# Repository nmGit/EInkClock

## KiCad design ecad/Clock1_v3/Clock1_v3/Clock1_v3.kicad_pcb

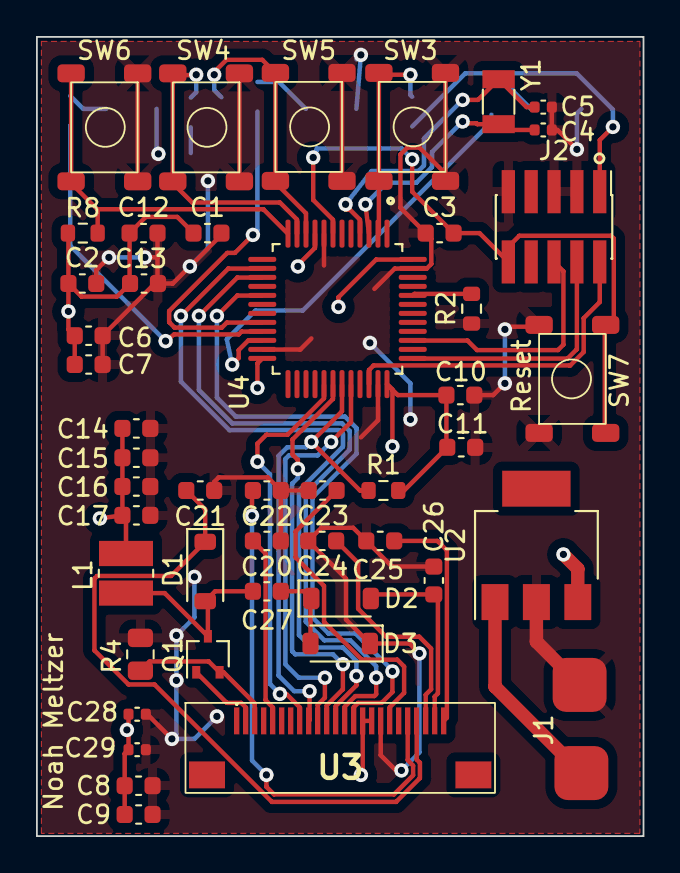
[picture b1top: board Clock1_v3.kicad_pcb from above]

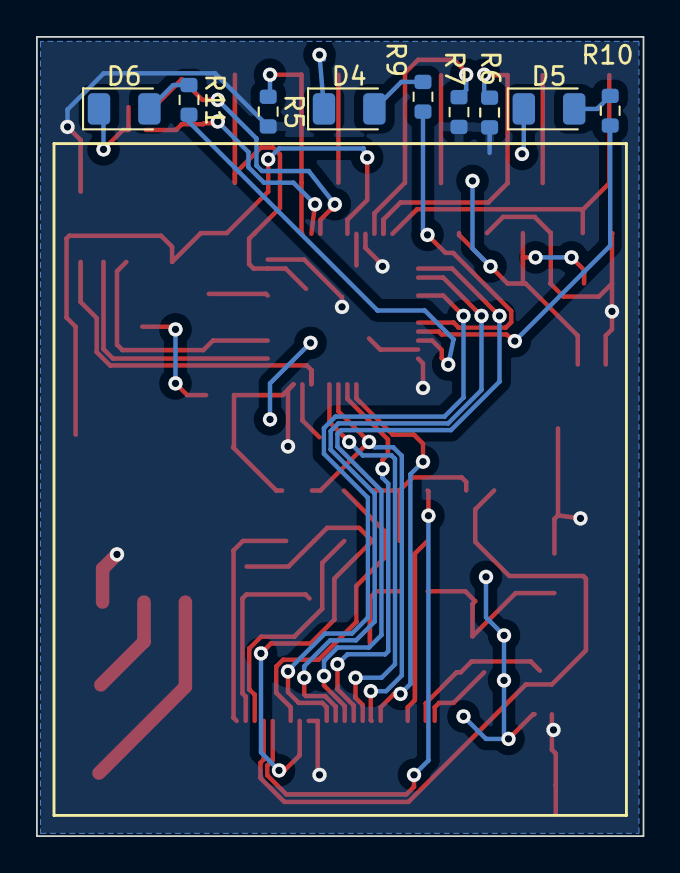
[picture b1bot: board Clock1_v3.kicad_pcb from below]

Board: 2 copper layers, 33.7 x 44.4 mm, 56 parts (9 on the bottom side), 38 nets.

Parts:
C1, C3, C6, C7, C8, C9, C10, C11, C12, C13, C14, C15, C16, C17: 100nf; C_0603_1608Metric
C2: 1uf; C_0603_1608Metric
C4, C5: 10pf; C_0402_1005Metric
C20, C21, C22, C23, C24, C25, C26: 1uF / 25V; C_0603_1608Metric
C27: 4.7uF / 25V; C_0603_1608Metric
C28: 1uF / 6.3V; C_0402_1005Metric
C29: 0.1uF / 16V; C_0402_1005Metric
D1, D2, D3: SD103AW; D_SOD-123
D4, D5, D6: LED; LED_1206_3216Metric
J1: Barrel_Jack; PowerPads
J2: Conn_ARM_JTAG_SWD_10; PinHeader_2x05_P1.27mm_Vertical_SMD
L1: 10uH; L_Ferrocore_DLG-0302
Q1: NMOS; SOT-323_SC-70
R1, R5, R6, R7, R8: 1K; R_0603_1608Metric
R2: 10K; R_0603_1608Metric
R4: 0.47R; R_0805_2012Metric
R9, R10, R11: 470; R_0603_1608Metric
SW3, SW4, SW5, SW6, SW7: SW_Push; PTS526
U2: SOT-223
U3: KH-FG0.5-H2.0-24PIN
U4: STM32F103C8T6; LQFP-48
Y1: 32k; Crystal_SMD_3215-2Pin_3.2x1.5mm

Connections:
/BOOT0: R2.2, U4.44 (BOOT0)
/LED1: R11.2, U4.22 (PB11)
/LED2: R10.2, U4.21 (PB10)
/LED3: R9.2, U4.20 (PB2)
/OSC32_IN: C4.2, U4.3 (PC14-OSC32_IN), Y1.1
/OSC32_OUT: C5.2, U4.4 (PC15-OSC32_OUT), Y1.2
/PB1: R5.1, SW3.2, U4.2 (PC13-TAMPER-RTC)
/PB2: R6.1, SW4.2, U4.11 (PA1)
/PB3: R7.1, SW5.2, U4.10 (PA0_WKUP)
/PB4: R8.1, SW6.2, U4.12 (PA2)
/SWDCLK: J2.4 (SWDCLK/TCK), U4.37 (PA14)
/SWDIO: J2.2 (SWDIO/TMS), U4.34 (PA13)
/SWO: J2.6 (SWO/TDO), U4.39 (PB3)
/epaper/epaper.gpio_bs: U3.8 (BS), U4.29 (PA8)
/epaper/epaper.gpio_busy_n: R1.1, U3.9 (BUSY), U4.31 (PA10)
/epaper/epaper.gpio_dc: U3.11 (D/C), U4.30 (PA9)
/epaper/epaper.gpio_reset_n: U3.10 (RESET), U4.32 (PA11)
/epaper/epaper.spi_cs: U3.12 (CS), U4.14 (PA4)
/epaper/epaper.spi_scl: U3.13 (SCL), U4.15 (PA5)
/epaper/epaper.spi_sda: U3.14 (SDA), U4.17 (PA7)
/nRESET: C3.2, J2.10 (~RESET), SW7.2, U4.7 (NRST)
GND: C1.2, C2.2, C3.1, C4.1, C5.1, C6.2, C7.2, C8.2, C9.2, C10.2, C11.2, C12.2, C13.2, C14.2, C15.2, C16.2, C17.2, C20.1, C21.1, C22.1, C23.1, C24.1, C25.1, C26.1, C28.2, C29.2, D3.1 (K), D4.1 (K), D5.1 (K), D6.1 (K), J1.2, J2.3 (GND), J2.5 (GND), J2.9 (GNDDetect), R2.1, R4.1, SW3.1, SW4.1, SW5.1, SW6.1, SW7.1, U2.2 (GND), U3.17 (GND), U4.8 (VSSA), U4.23 (VSS), U4.35 (VSS__1), U4.47 (VSS__2)
unnamed: C27.1, D1.2 (A), L1.2, Q1.3 (D)
unnamed: C21.2, D1.1 (K), U3.21 (VGH)
unnamed: C26.2, D2.2 (A), U3.23 (VGL)
unnamed: C27.2, D2.1 (K), D3.2 (A)
unnamed: D4.2 (A), R9.1
unnamed: D5.2 (A), R10.1
unnamed: D6.2 (A), R11.1
unnamed: Q1.1 (G), U3.2 (GDR)
unnamed: Q1.2 (S), R4.2, U3.3 (RSE)
unnamed: C25.2, U3.24 (VCOM)
unnamed: C23.2, U3.18 (VDDD)
unnamed: C22.2, U3.20 (VDH)
unnamed: C24.2, U3.22 (VDL)
unnamed: C20.2, U3.5 (VHDR)
VDD: C1.1, C2.1, C6.1, C7.1, C8.1, C9.1, C10.1, C11.1, C12.1, C13.1, C14.1, C15.1, C16.1, C17.1, C28.1, C29.1, J2.1 (VTref), L1.1, R1.2, R5.2, R6.2, R7.2, R8.2, U2.3 (Vout), U3.15 (VDDIO), U3.16 (VDDA), U4.9 (VDDA), U4.24 (VDD), U4.36 (VDD__1), U4.48 (VDD__2)
Vin: J1.1, U2.1 (Vin)

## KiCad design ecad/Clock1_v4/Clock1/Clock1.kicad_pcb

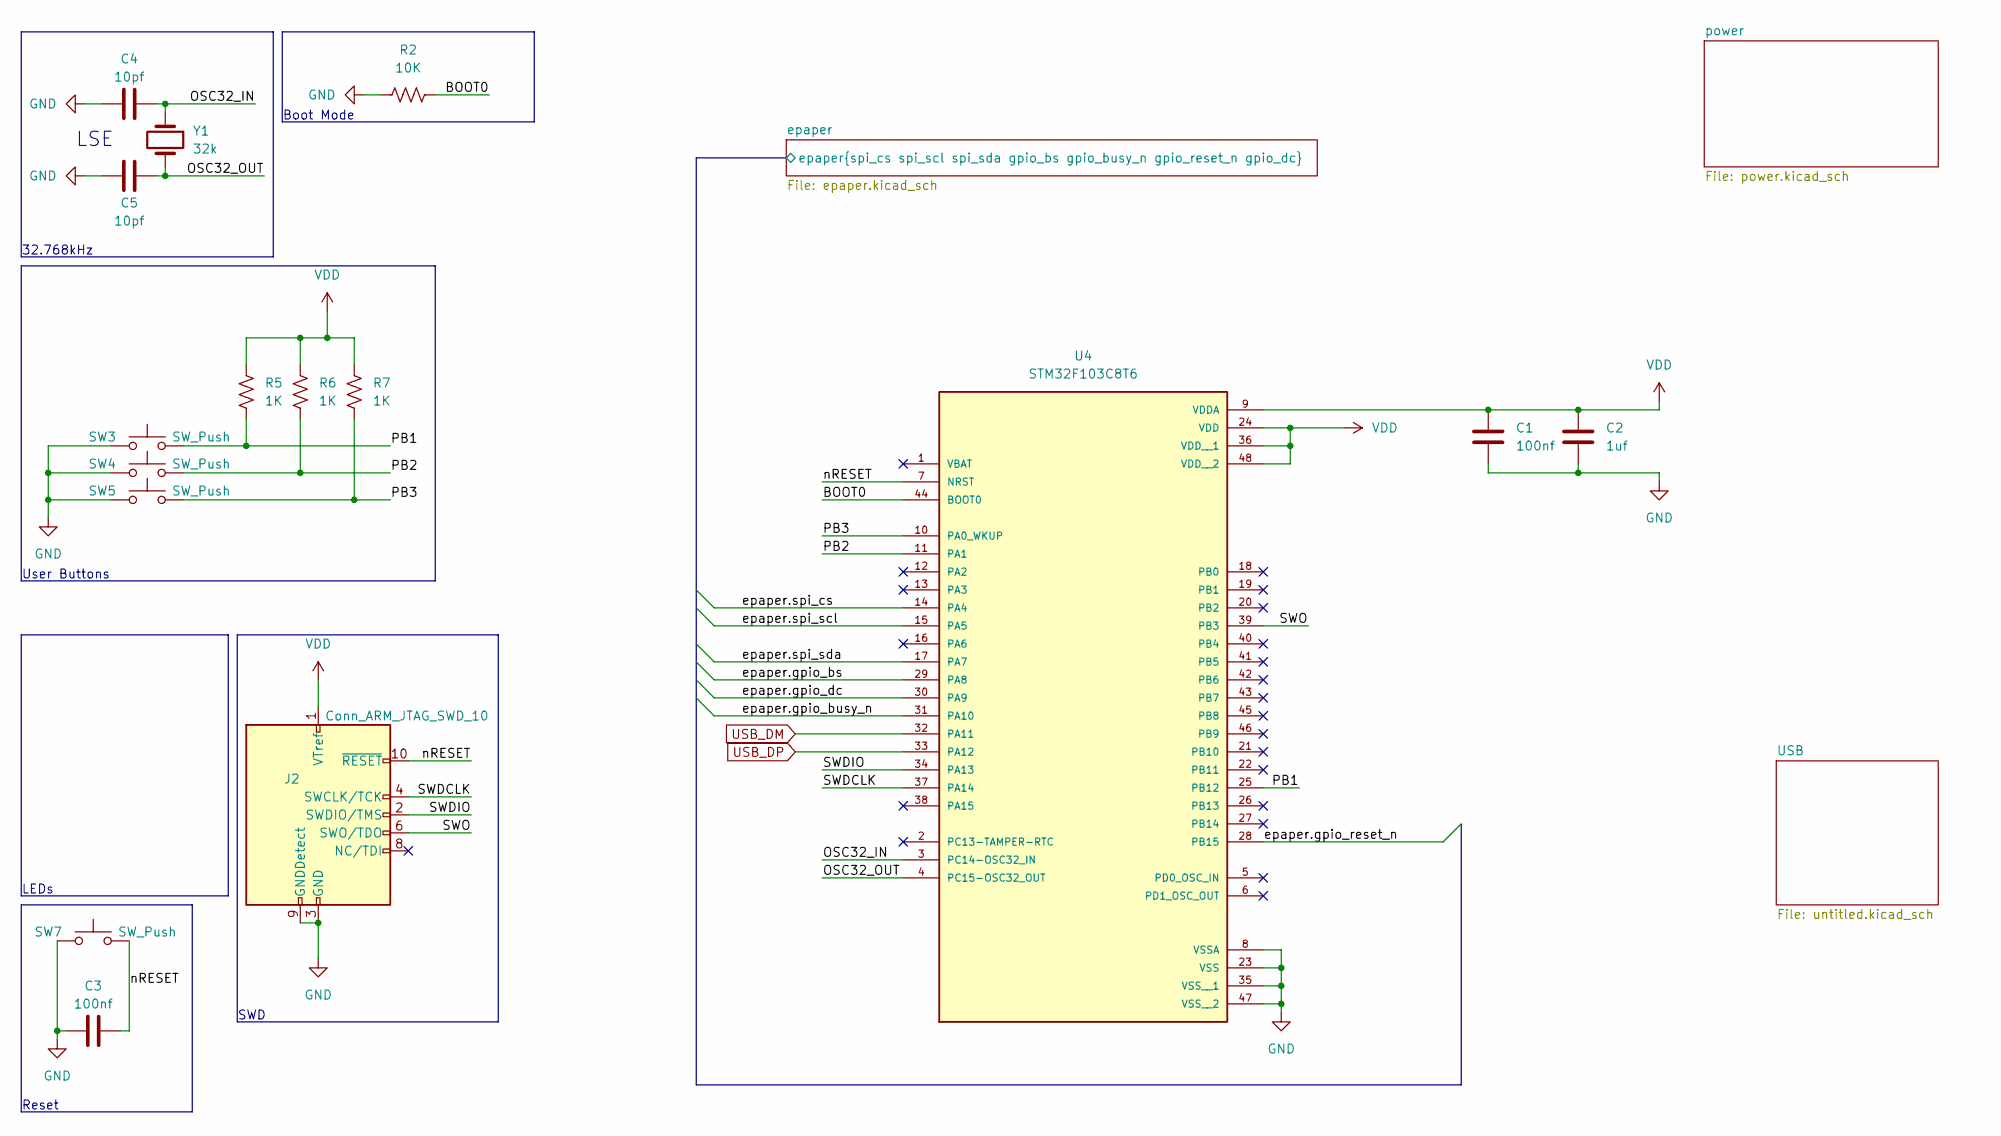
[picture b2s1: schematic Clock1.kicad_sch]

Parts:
C1, C3: 100nf; C_0603_1608Metric; Part Number KAM15AR71H104KT; JLCPCB Part # C14663
C2: 1uf; C_0603_1608Metric; Part Number MSASU168AB7105KTNA01; JLCPCB Part # C90540
C4, C5: 10pf; C_0402_1005Metric; Part Number C0402C0G100J500NTB; JLCPCB Part # C115606
J2: Conn_ARM_JTAG_SWD_10; PinHeader_2x05_P1.27mm_Vertical_SMD; Part Number 20021121-00010T4LF; JLCPCB Part # C598540
R2: 10K; R_0603_1608Metric; Part Number CRCW060310K0DHEAP; JLCPCB Part # C25804
R5, R6, R7: 1K; R_0603_1608Metric; Part Number AC0603JR-071KL; JLCPCB Part # C144622
SW3, SW4, SW5, SW7: SW_Push; PTS526; Part Number PTS526SM15SMTR2LFS; JLCPCB Part # C2689538
U4: STM32F103C8T6; LQFP-48; PARTREV 10; JLCPCB Part # C8734
Y1: 32k; Crystal_SMD_3215-2Pin_3.2x1.5mm; Part Number SF32K32768D91T-B; JLCPCB Part # C907542

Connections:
/BOOT0: R2.2, U4.44 (BOOT0)
/OSC32_IN: C4.2, U4.3 (PC14-OSC32_IN), Y1.1
/OSC32_OUT: C5.2, U4.4 (PC15-OSC32_OUT), Y1.2
/PB1: R5.1, SW3.2, U4.25 (PB12)
/PB2: R6.1, SW4.2, U4.11 (PA1)
/PB3: R7.1, SW5.2, U4.10 (PA0_WKUP)
/SWDCLK: J2.4 (SWCLK/TCK), U4.37 (PA14)
/SWDIO: J2.2 (SWDIO/TMS), U4.34 (PA13)
/SWO: J2.6 (SWO/TDO), U4.39 (PB3)
/epaper/epaper.gpio_bs: U4.29 (PA8); also elsewhere on the board
/epaper/epaper.gpio_busy_n: U4.31 (PA10); also elsewhere on the board
/epaper/epaper.gpio_dc: U4.30 (PA9); also elsewhere on the board
/epaper/epaper.gpio_reset_n: U4.28 (PB15); also elsewhere on the board
/epaper/epaper.spi_cs: U4.14 (PA4); also elsewhere on the board
/epaper/epaper.spi_scl: U4.15 (PA5); also elsewhere on the board
/epaper/epaper.spi_sda: U4.17 (PA7); also elsewhere on the board
/nRESET: C3.2, J2.10 (~RESET), SW7.2, U4.7 (NRST)
GND: C1.2, C2.2, C3.1, C4.1, C5.1, J2.3 (GND), J2.5 (GND), J2.9 (GNDDetect), R2.1, SW3.1, SW4.1, SW5.1, SW7.1, U4.8 (VSSA), U4.23 (VSS), U4.35 (VSS__1), U4.47 (VSS__2); also elsewhere on the board
USB_DM: U4.32 (PA11); also elsewhere on the board
USB_DP: U4.33 (PA12); also elsewhere on the board
VDD: C1.1, C2.1, J2.1 (VTref), R5.2, R6.2, R7.2, U4.9 (VDDA), U4.24 (VDD), U4.36 (VDD__1), U4.48 (VDD__2); also elsewhere on the board

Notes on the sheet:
Boot Mode
User Buttons
LSE
32.768kHz
SWD
LEDs
Reset

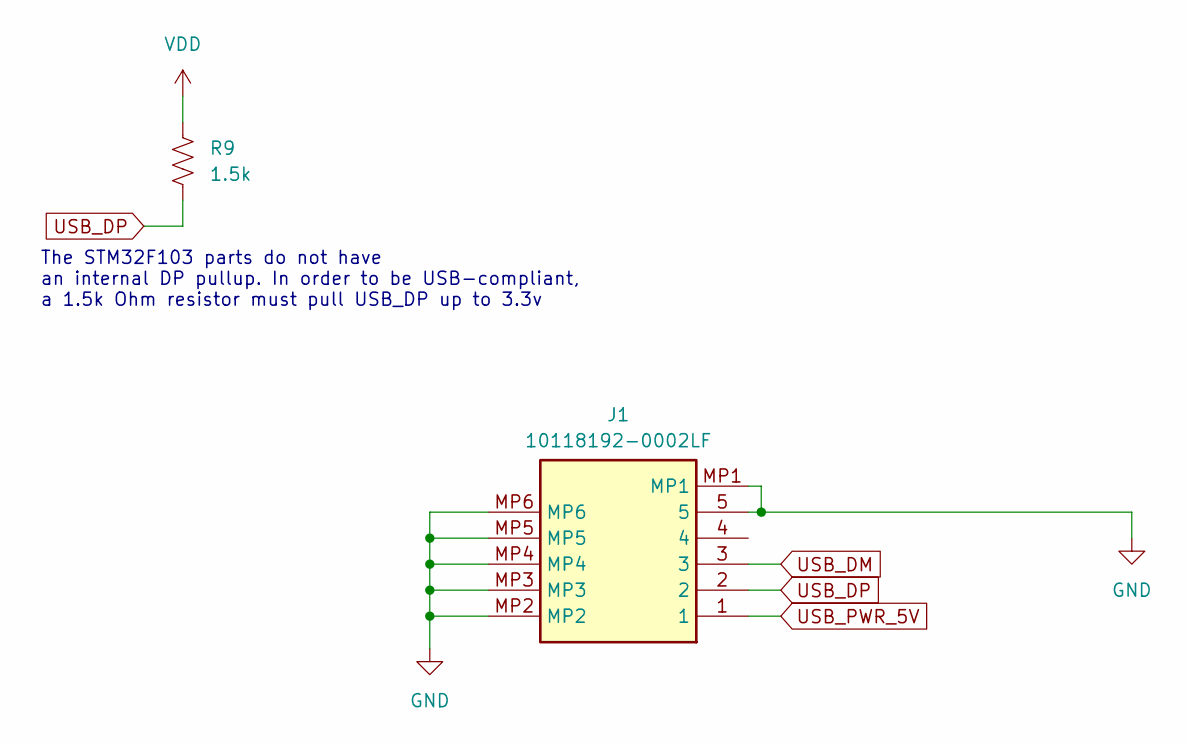
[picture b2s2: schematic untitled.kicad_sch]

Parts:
J1: 10118192-0002LF; 101181920002LF; Manufacturer_Part_Number 10118192-0002LF; JLCPCB Part # C2972784
R9: 1.5k; R_0402_1005Metric; Part Number RTT021501FTH; JLCPCB Part # C102811

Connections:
GND: J1.5, J1.MP1, J1.MP2, J1.MP3, J1.MP4, J1.MP5, J1.MP6; also elsewhere on the board
USB_DM: J1.3; also elsewhere on the board
USB_DP: J1.2, R9.2; also elsewhere on the board
USB_PWR_5V: J1.1; also elsewhere on the board
VDD: R9.1; also elsewhere on the board

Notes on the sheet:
The STM32F103 parts do not have an internal DP pullup. In order to be USB-compliant, a 1.5k Ohm resistor must pull USB_DP up to 3.3v

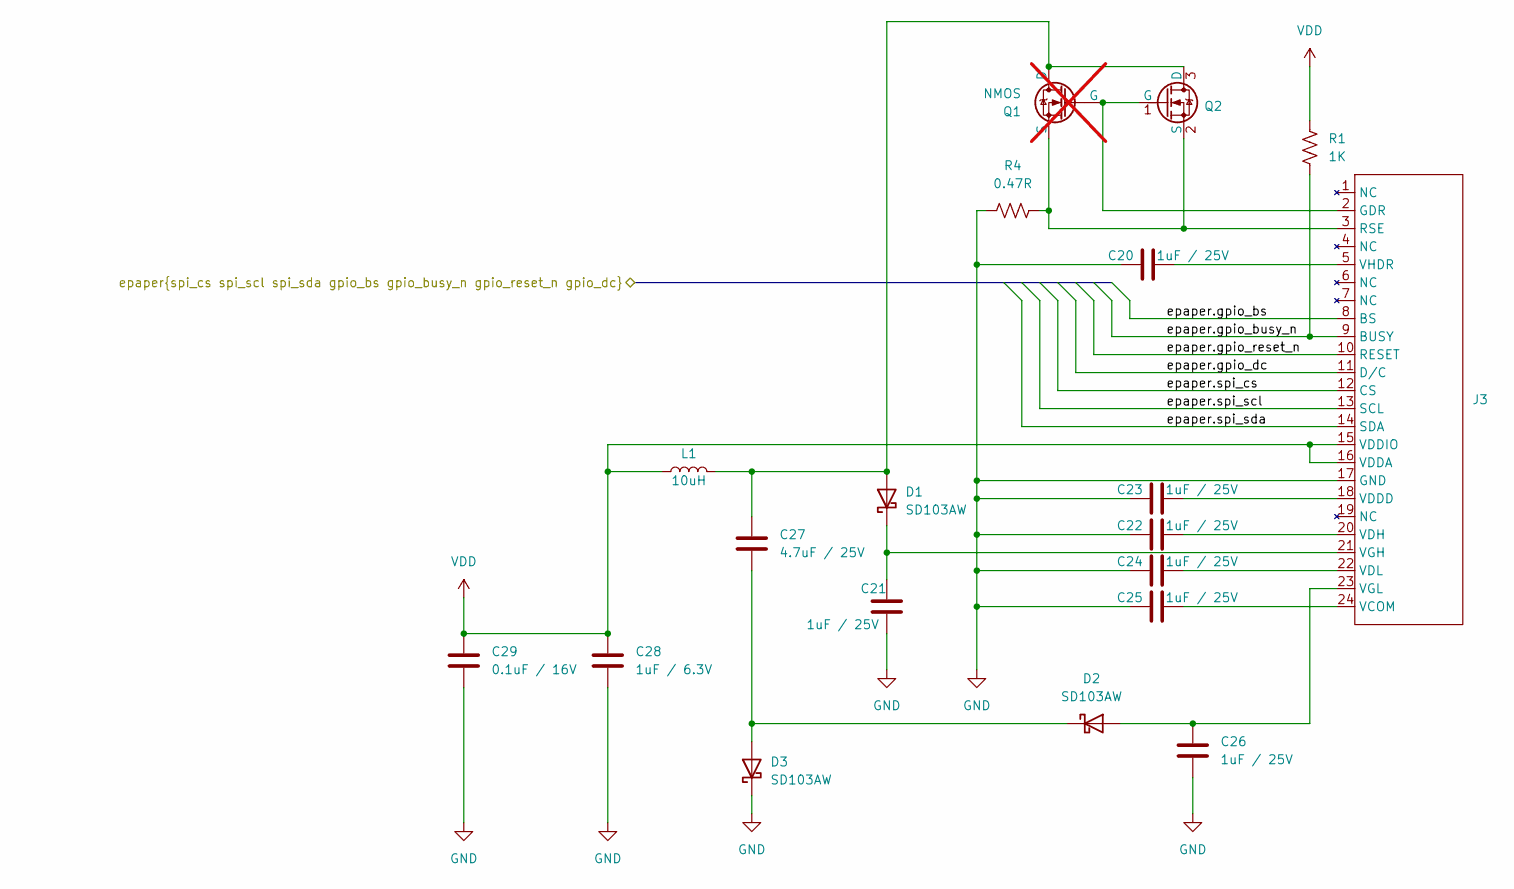
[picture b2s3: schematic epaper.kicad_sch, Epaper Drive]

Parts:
C20, C21, C22, C23, C24, C25, C26: 1uF / 25V; C_0603_1608Metric; Part Number CC0603KRX7R8BB105; JLCPCB Part # C106858
C27: 4.7uF / 25V; C_0603_1608Metric; Part Number C1608X5R1E475KT000E; JLCPCB Part # C76615
C28: 1uF / 6.3V; C_0402_1005Metric; Part Number C1005X5R105KCT; JLCPCB Part # C258509
C29: 0.1uF / 16V; C_0402_1005Metric; Part Number V105K0402X5R160NBT; JLCPCB Part # C3009903
D1, D2, D3: SD103AW; D_SOD-123; Part Number SD103AW; JLCPCB Part # C181204
J3: KH-FG0.5-H2.0-24PIN; Part Number KH-FG0.5-H2.0-24PIN; JLCPCB Part # C2797213
L1: 10uH; L_Ferrocore_DLG-0302; Part Number CD32YP0302-100M; JLCPCB Part # C492261
Q1: NMOS; SOT-323_SC-70; Part Number RTF016N05TL; JLCPCB Part # C3282000; not fitted
Q2: SOT-23; Part Number PJM02N60SA; JLCPCB Part # C2856840
R1: 1K; R_0603_1608Metric; Part Number AC0603JR-071KL; JLCPCB Part # C144622
R4: 0.47R; R_0805_2012Metric; Part Number ERJ-U6QJR47V; JLCPCB Part # C491238

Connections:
/epaper/epaper.gpio_bs: J3.8 (BS); also elsewhere on the board
/epaper/epaper.gpio_busy_n: J3.9 (BUSY), R1.1; also elsewhere on the board
/epaper/epaper.gpio_dc: J3.11 (D/C); also elsewhere on the board
/epaper/epaper.gpio_reset_n: J3.10 (RESET); also elsewhere on the board
/epaper/epaper.spi_cs: J3.12 (CS); also elsewhere on the board
/epaper/epaper.spi_scl: J3.13 (SCL); also elsewhere on the board
/epaper/epaper.spi_sda: J3.14 (SDA); also elsewhere on the board
GND: C20.1, C21.1, C22.1, C23.1, C24.1, C25.1, C26.1, C28.2, C29.2, D3.1 (K), J3.17 (GND), R4.1; also elsewhere on the board
unnamed: C27.1, D1.2 (A), L1.2, Q1.1 (D), Q2.3 (D)
unnamed: C21.2, D1.1 (K), J3.21 (VGH)
unnamed: C26.2, D2.2 (A), J3.23 (VGL)
unnamed: C27.2, D2.1 (K), D3.2 (A)
unnamed: J3.2 (GDR), Q1.2 (G), Q2.1 (G)
unnamed: J3.3 (RSE), Q1.3 (S), Q2.2 (S), R4.2
unnamed: C25.2, J3.24 (VCOM)
unnamed: C23.2, J3.18 (VDDD)
unnamed: C22.2, J3.20 (VDH)
unnamed: C24.2, J3.22 (VDL)
unnamed: C20.2, J3.5 (VHDR)
VDD: C28.1, C29.1, J3.15 (VDDIO), J3.16 (VDDA), L1.1, R1.2; also elsewhere on the board

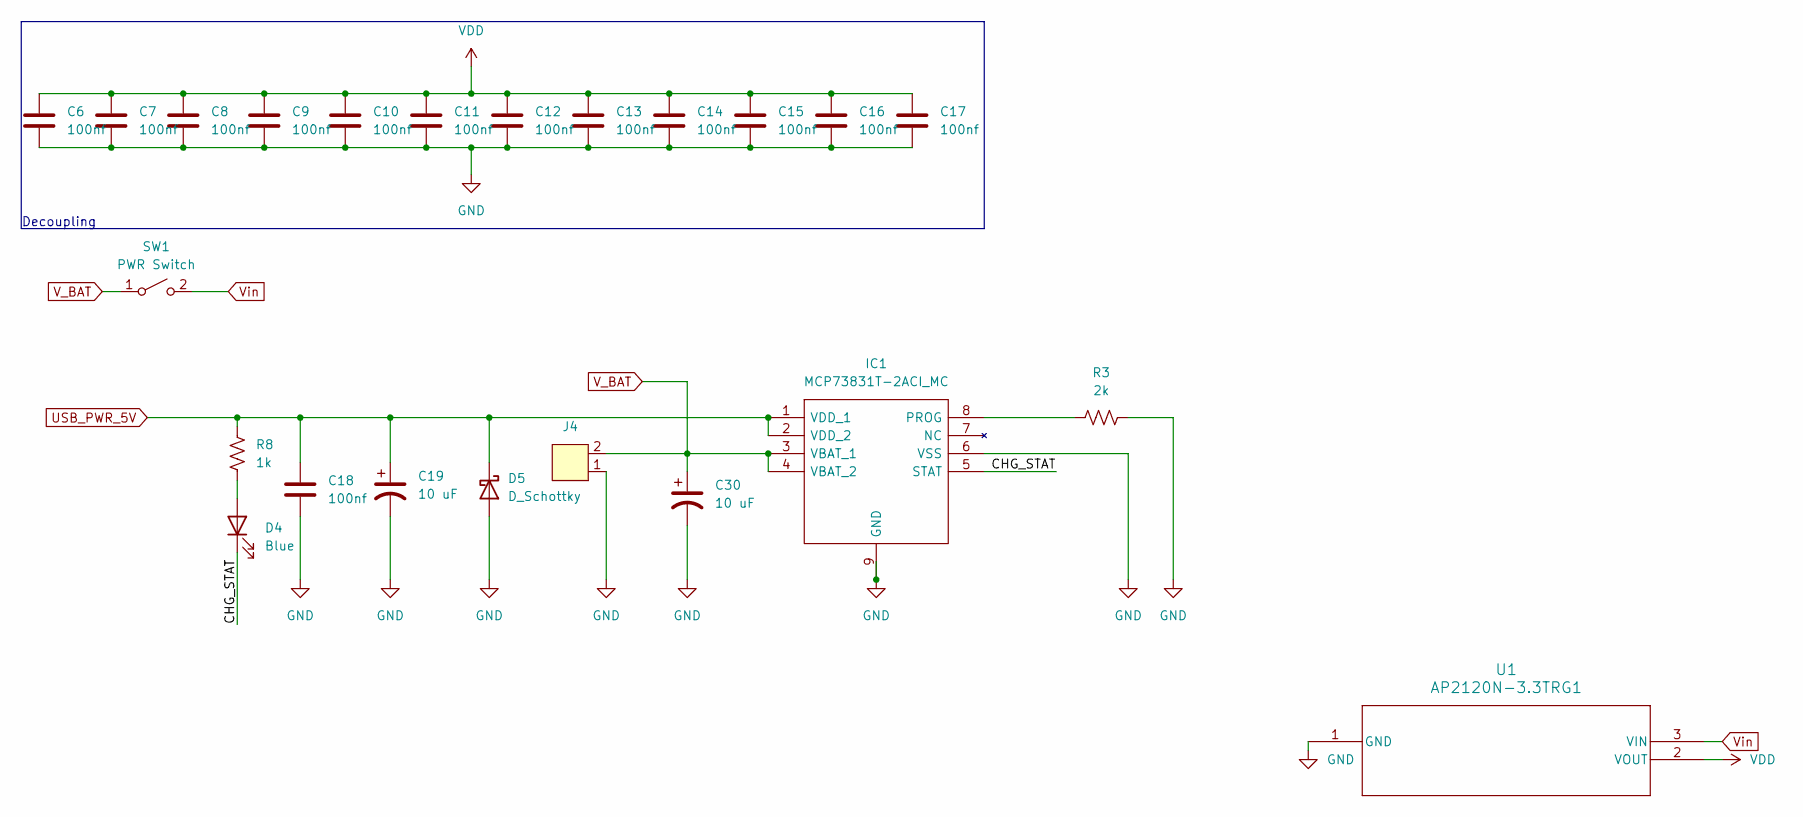
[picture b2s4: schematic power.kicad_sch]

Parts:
C6, C7, C8, C9, C10, C11, C12, C13, C14, C15, C16, C17, C18: 100nf; C_0603_1608Metric; Part Number KAM15AR71H104KT; JLCPCB Part # C14663
C19, C30: 10 uF; C_0805_2012Metric; JLCPCB Part # C692636
D4: Blue; LED_0402_1005Metric; JLCPCB Part # C2856703
D5: D_Schottky; D_SMA; JLCPCB Part # C98802
IC1: MCP73831T-2ACI_MC; SON50P300X200X100-9N-D; Mouser Part Number 579-MCP73831T-2ACIMC
J4: BM02B-SRSS-TB; JLCPCB Part # C160388
R3: 2k; R_0402_1005Metric; JLCPCB Part # C144035
R8: 1k; R_0402_1005Metric; Part Number RC0402FR-071KL; JLCPCB Part # C106235
SW1: PWR Switch; HX MSK12CO2-BBTM; JLCPCB Part # C5149818
U1: AP2120N-3.3TRG1; SOT-23_DIO; JLCPCB Part # C156330

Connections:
/power/CHG_STAT: D4.1 (K), IC1.5 (STAT)
GND: C6.2, C7.2, C8.2, C9.2, C10.2, C11.2, C12.2, C13.2, C14.2, C15.2, C16.2, C17.2, C18.2, C19.2, C30.2, D5.2 (A), IC1.6 (VSS), IC1.9 (GND), J4.1, R3.2, U1.1 (GND); also elsewhere on the board
unnamed: D4.2 (A), R8.2
unnamed: IC1.8 (PROG), R3.1
USB_PWR_5V: C18.1, C19.1, D5.1 (K), IC1.1 (VDD_1), IC1.2 (VDD_2), R8.1; also elsewhere on the board
VDD: C6.1, C7.1, C8.1, C9.1, C10.1, C11.1, C12.1, C13.1, C14.1, C15.1, C16.1, C17.1, U1.2 (VOUT); also elsewhere on the board
V_BAT: C30.1, IC1.3 (VBAT_1), IC1.4 (VBAT_2), J4.2, SW1.1 (A)
Vin: SW1.2 (B), U1.3 (VIN)

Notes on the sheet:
Decoupling

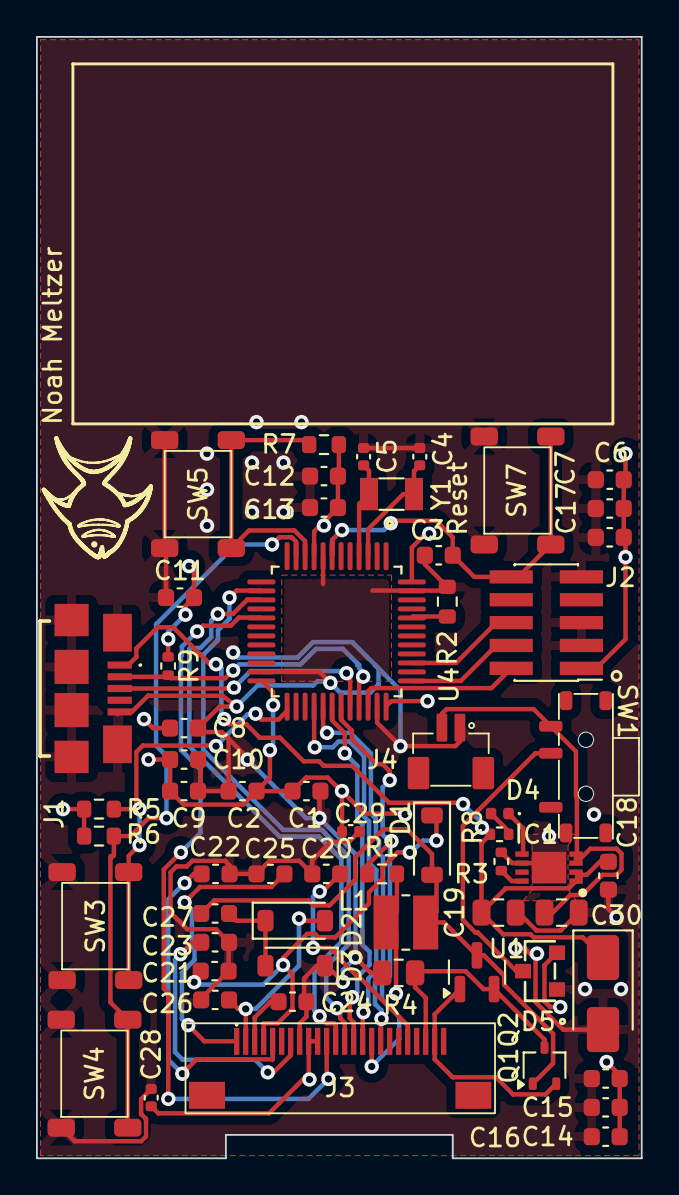
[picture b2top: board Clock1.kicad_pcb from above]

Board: 2 copper layers, 33.6 x 62.3 mm, 60 parts (0 on the bottom side), 38 nets.

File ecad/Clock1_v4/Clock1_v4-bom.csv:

Designator,Comment,Footprint,Qty,LCSC Part Number,Part Number
Y1,32k,Crystal:Crystal_SMD_3215-2Pin_3.2x1.5mm,1,C907542,SF32K32768D91T-B
U4,STM32F103C8T6,NoahsFootprints:LQFP-48,1,C8734,STM32F103C8T6
U1,AP2120N-3.3TRG1,SOT-23_DIO,1,C156330,
SW7,SW_Push,NoahsFootprints:PTS526,1,C2689538,PTS526SM15SMTR2LFS
SW5,SW_Push,NoahsFootprints:PTS526,1,C2689538,PTS526SM15SMTR2LFS
SW4,SW_Push,NoahsFootprints:PTS526,1,C2689538,PTS526SM15SMTR2LFS
SW3,SW_Push,NoahsFootprints:PTS526,1,C2689538,PTS526SM15SMTR2LFS
SW1,PWR Switch,NoahsFootprints:HX MSK12CO2-BBTM,1,C5149818,
R9,1.5k,Resistor_SMD:R_0402_1005Metric,1,C102811,RTT021501FTH
R8,1k,Resistor_SMD:R_0402_1005Metric,1,C106235,RC0402FR-071KL
R7,1K,Resistor_SMD:R_0603_1608Metric,1,C144622,AC0603JR-071KL
R6,1K,Resistor_SMD:R_0603_1608Metric,1,C144622,AC0603JR-071KL
R5,1K,Resistor_SMD:R_0603_1608Metric,1,C144622,AC0603JR-071KL
R4,0.47R,Resistor_SMD:R_0805_2012Metric,1,C491238,ERJ-U6QJR47V
R3,2k,Resistor_SMD:R_0402_1005Metric,1,C144035,
R2,10K,Resistor_SMD:R_0603_1608Metric,1,C25804,CRCW060310K0DHEAP
R1,1K,Resistor_SMD:R_0603_1608Metric,1,C144622,AC0603JR-071KL
Q2,~,Package_TO_SOT_SMD:SOT-23,1,C2856840,PJM02N60SA
L1,10uH,Inductor_SMD:L_Ferrocore_DLG-0302,1,C492261,CD32YP0302-100M
J4,~,NoahsFootprints:BM02B-SRSS-TB,1,C160388,
J3,~,NoahsFootprints:KH-FG0.5-H2.0-24PIN,1,C2797213,KH-FG0.5-H2.0-24PIN
J2,Conn_ARM_JTAG_SWD_10,Connector_PinHeader_1.27mm:PinHeader_2x05_P1.27mm_Vertical_SMD,1,C598540,20021121-00010T4LF
J1,10118192-0002LF,NoahsFootprints:101181920002LF,1,C2972784,
IC1,MCP73831T-2ACI_MC,NoahsFootprints:SON50P300X200X100-9N-D,1,C411870,
D5,D_Schottky,Diode_SMD:D_SMA,1,C98802,
D4,Blue,LED_SMD:LED_0402_1005Metric,1,C2856703,
D3,SD103AW,Diode_SMD:D_SOD-123,1,C181204,SD103AW
D2,SD103AW,Diode_SMD:D_SOD-123,1,C181204,SD103AW
D1,SD103AW,Diode_SMD:D_SOD-123,1,C181204,SD103AW
C30,10 uF,Capacitor_SMD:C_0805_2012Metric,1,C692636,
C29,0.1uF / 16V,Capacitor_SMD:C_0402_1005Metric,1,C3009903,V105K0402X5R160NBT
C28,1uF / 6.3V,Capacitor_SMD:C_0402_1005Metric,1,C258509,C1005X5R105KCT
C27,4.7uF / 25V,Capacitor_SMD:C_0603_1608Metric,1,C76615,C1608X5R1E475KT000E
C26,1uF / 25V,Capacitor_SMD:C_0603_1608Metric,1,C106858,CC0603KRX7R8BB105
C25,1uF / 25V,Capacitor_SMD:C_0603_1608Metric,1,C106858,CC0603KRX7R8BB105
C24,1uF / 25V,Capacitor_SMD:C_0603_1608Metric,1,C106858,CC0603KRX7R8BB105
C23,1uF / 25V,Capacitor_SMD:C_0603_1608Metric,1,C106858,CC0603KRX7R8BB105
C22,1uF / 25V,Capacitor_SMD:C_0603_1608Metric,1,C106858,CC0603KRX7R8BB105
C21,1uF / 25V,Capacitor_SMD:C_0603_1608Metric,1,C106858,CC0603KRX7R8BB105
C20,1uF / 25V,Capacitor_SMD:C_0603_1608Metric,1,C106858,CC0603KRX7R8BB105
C19,10 uF,Capacitor_SMD:C_0805_2012Metric,1,C692636,
C18,100nf,Capacitor_SMD:C_0603_1608Metric,1,C14663,KAM15AR71H104KT
C17,100nf,Capacitor_SMD:C_0603_1608Metric,1,C14663,KAM15AR71H104KT
C16,100nf,Capacitor_SMD:C_0603_1608Metric,1,C14663,KAM15AR71H104KT
C15,100nf,Capacitor_SMD:C_0603_1608Metric,1,C14663,KAM15AR71H104KT
C14,100nf,Capacitor_SMD:C_0603_1608Metric,1,C14663,KAM15AR71H104KT
C13,100nf,Capacitor_SMD:C_0603_1608Metric,1,C14663,KAM15AR71H104KT
C12,100nf,Capacitor_SMD:C_0603_1608Metric,1,C14663,KAM15AR71H104KT
C11,100nf,Capacitor_SMD:C_0603_1608Metric,1,C14663,KAM15AR71H104KT
C10,100nf,Capacitor_SMD:C_0603_1608Metric,1,C14663,KAM15AR71H104KT
C9,100nf,Capacitor_SMD:C_0603_1608Metric,1,C14663,KAM15AR71H104KT
C8,100nf,Capacitor_SMD:C_0603_1608Metric,1,C14663,KAM15AR71H104KT
C7,100nf,Capacitor_SMD:C_0603_1608Metric,1,C14663,KAM15AR71H104KT
C6,100nf,Capacitor_SMD:C_0603_1608Metric,1,C14663,KAM15AR71H104KT
C5,10pf,Capacitor_SMD:C_0402_1005Metric,1,C115606,C0402C0G100J500NTB
C4,10pf,Capacitor_SMD:C_0402_1005Metric,1,C115606,C0402C0G100J500NTB
C3,100nf,Capacitor_SMD:C_0603_1608Metric,1,C14663,KAM15AR71H104KT
C2,1uf,Capacitor_SMD:C_0603_1608Metric,1,C90540,MSASU168AB7105KTNA01
C1,100nf,Capacitor_SMD:C_0603_1608Metric,1,C14663,KAM15AR71H104KT

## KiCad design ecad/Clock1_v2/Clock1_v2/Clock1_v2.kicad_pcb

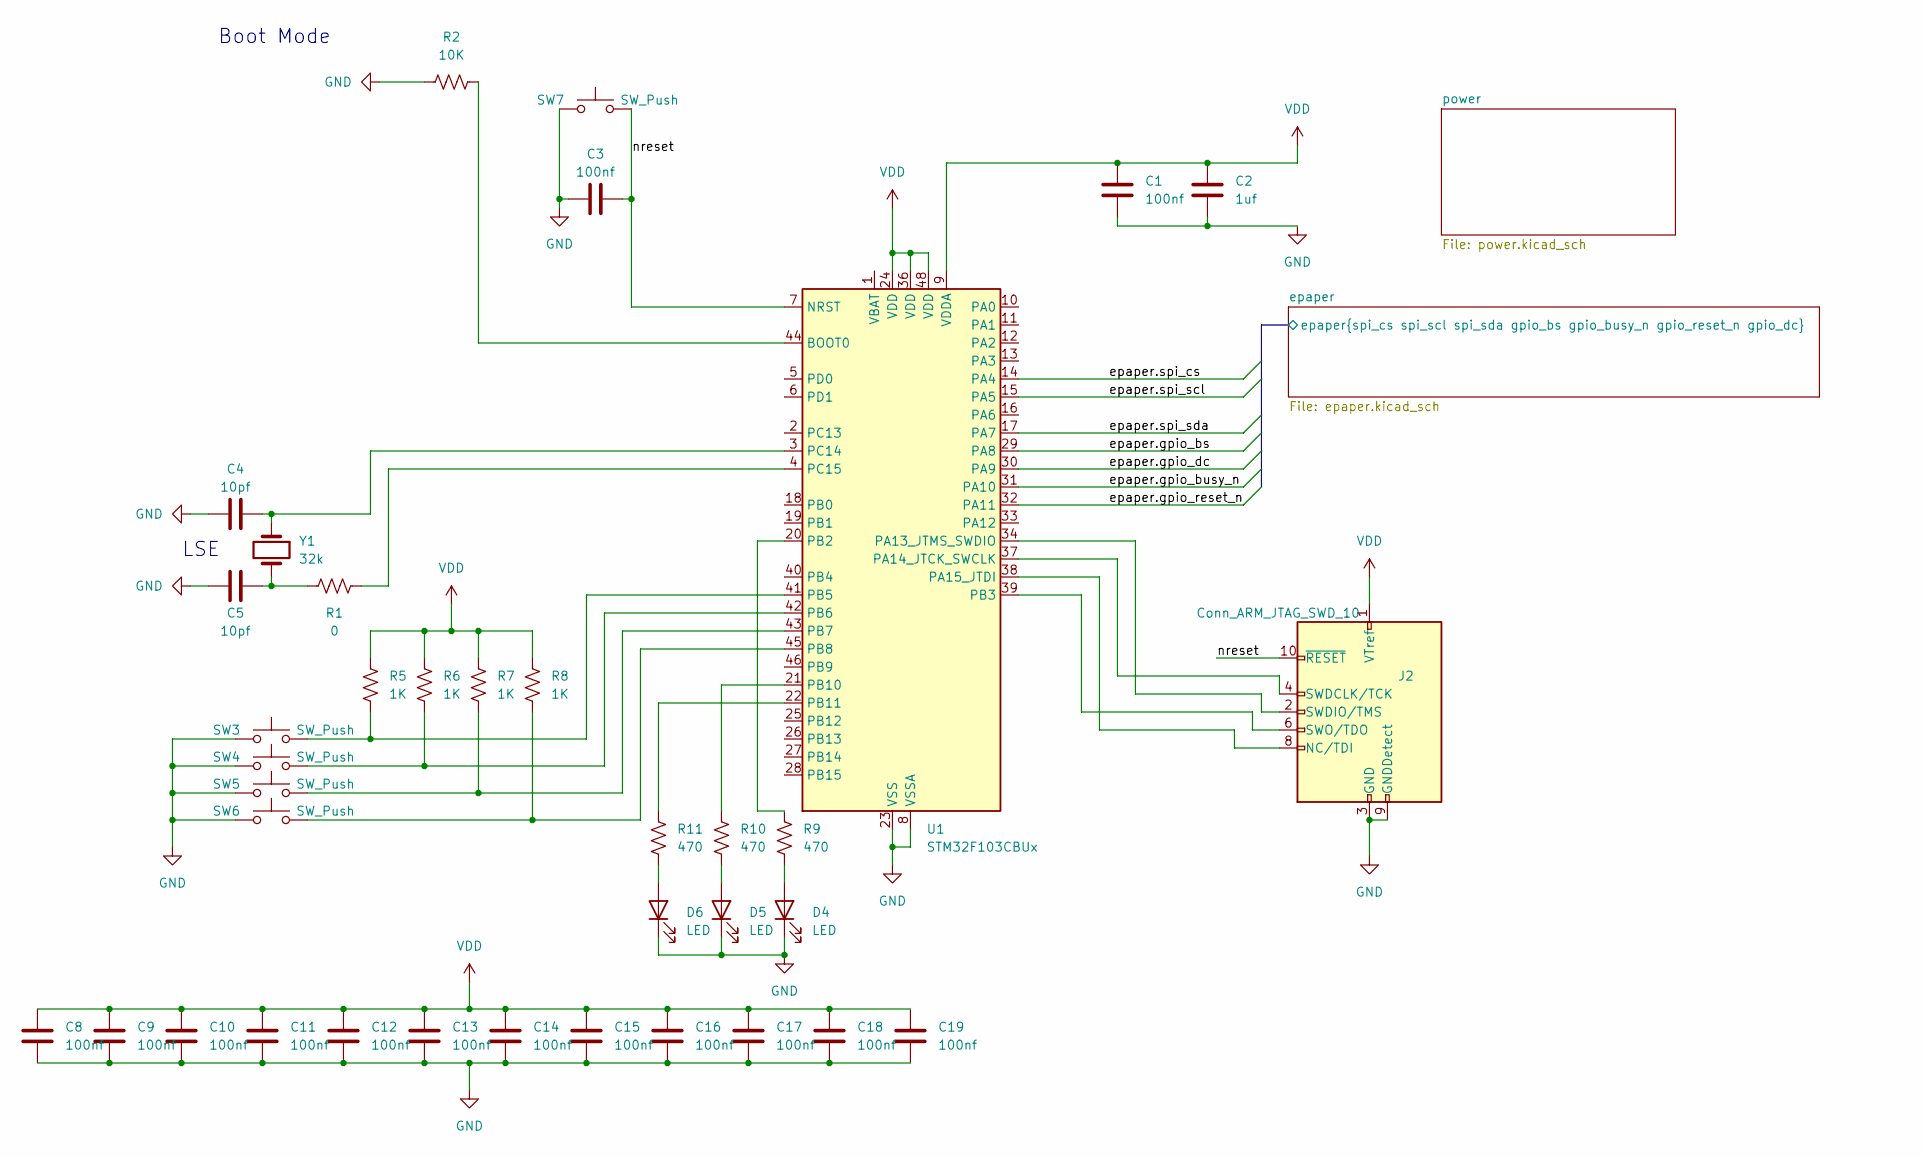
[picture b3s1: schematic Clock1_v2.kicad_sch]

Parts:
C1, C3, C8, C9, C10, C11, C12, C13, C14, C15, C16, C17, C18, C19: 100nf; C_0603_1608Metric; Part Number KAM15AR71H104KT
C2: 1uf; C_0603_1608Metric; Part Number MSASU168AB7105KTNA01
C4, C5: 10pf; C_0201_0603Metric; Part Number 02013A100DAT2A
D4, D5, D6: LED; LED_1206_3216Metric; Part Number HSMA-C350
J2: Conn_ARM_JTAG_SWD_10; PinHeader_2x05_P1.27mm_Vertical_SMD; Part Number 20021121-00010T4LF
R1: 0; R_0603_1608Metric; Part Number CRCW06030000Z0EAC
R2: 10K; R_0603_1608Metric; Part Number CRCW060310K0DHEAP
R5, R6, R7, R8: 1K; R_0603_1608Metric; Part Number CRCW06031K00DHEBP
R9, R10, R11: 470; R_1206_3216Metric; Part Number MCT06030C4700FP500
SW3, SW4, SW5, SW6, SW7: SW_Push; PTS526; Part Number PTS526SMG20SMTR21 LFS
U1: STM32F103CBUx; QFN-48-1EP_7x7mm_P0.5mm_EP5.6x5.6mm; Part Number STM32F103CBU6
Y1: 32k; Crystal_SMD_TXC_9HT11-2Pin_2.0x1.2mm; Part Number FC2012SN 32.768K-90NNA0KC0

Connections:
/epaper/epaper.gpio_bs: U1.29 (PA8); also elsewhere on the board
/epaper/epaper.gpio_busy_n: U1.31 (PA10); also elsewhere on the board
/epaper/epaper.gpio_dc: U1.30 (PA9); also elsewhere on the board
/epaper/epaper.gpio_reset_n: U1.32 (PA11); also elsewhere on the board
/epaper/epaper.spi_cs: U1.14 (PA4); also elsewhere on the board
/epaper/epaper.spi_scl: U1.15 (PA5); also elsewhere on the board
/epaper/epaper.spi_sda: U1.17 (PA7); also elsewhere on the board
/nreset: C3.2, J2.10 (~RESET), SW7.2, U1.7 (NRST)
GND: C1.2, C2.2, C3.1, C4.1, C5.1, C8.2, C9.2, C10.2, C11.2, C12.2, C13.2, C14.2, C15.2, C16.2, C17.2, C18.2, C19.2, D4.1 (K), D5.1 (K), D6.1 (K), J2.3 (GND), J2.5 (GND), J2.9 (GNDDetect), R2.1, SW3.1, SW4.1, SW5.1, SW6.1, SW7.1, U1.8 (VSSA), U1.23 (VSS), U1.35 (VSS), U1.47 (VSS), U1.49 (VSS); also elsewhere on the board
unnamed: C5.2, R1.1, Y1.2
unnamed: D4.2 (A), R9.1
unnamed: D5.2 (A), R10.1
unnamed: D6.2 (A), R11.1
unnamed: J2.8 (NC/TDI), U1.38 (PA15_JTDI)
unnamed: J2.4 (SWDCLK/TCK), U1.37 (PA14_JTCK_SWCLK)
unnamed: J2.2 (SWDIO/TMS), U1.34 (PA13_JTMS_SWDIO)
unnamed: J2.6 (SWO/TDO), U1.39 (PB3)
unnamed: R2.2, U1.44 (BOOT0)
unnamed: R9.2, U1.20 (PB2)
unnamed: R5.1, SW3.2, U1.41 (PB5)
unnamed: R6.1, SW4.2, U1.42 (PB6)
unnamed: R7.1, SW5.2, U1.43 (PB7)
unnamed: R8.1, SW6.2, U1.45 (PB8)
unnamed: R10.2, U1.21 (PB10)
unnamed: R11.2, U1.22 (PB11)
unnamed: C4.2, U1.3 (PC14), Y1.1
unnamed: R1.2, U1.4 (PC15)
VDD: C1.1, C2.1, C8.1, C9.1, C10.1, C11.1, C12.1, C13.1, C14.1, C15.1, C16.1, C17.1, C18.1, C19.1, J2.1 (VTref), R5.2, R6.2, R7.2, R8.2, U1.9 (VDDA), U1.24 (VDD), U1.36 (VDD), U1.48 (VDD); also elsewhere on the board

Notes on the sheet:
LSE
Boot Mode

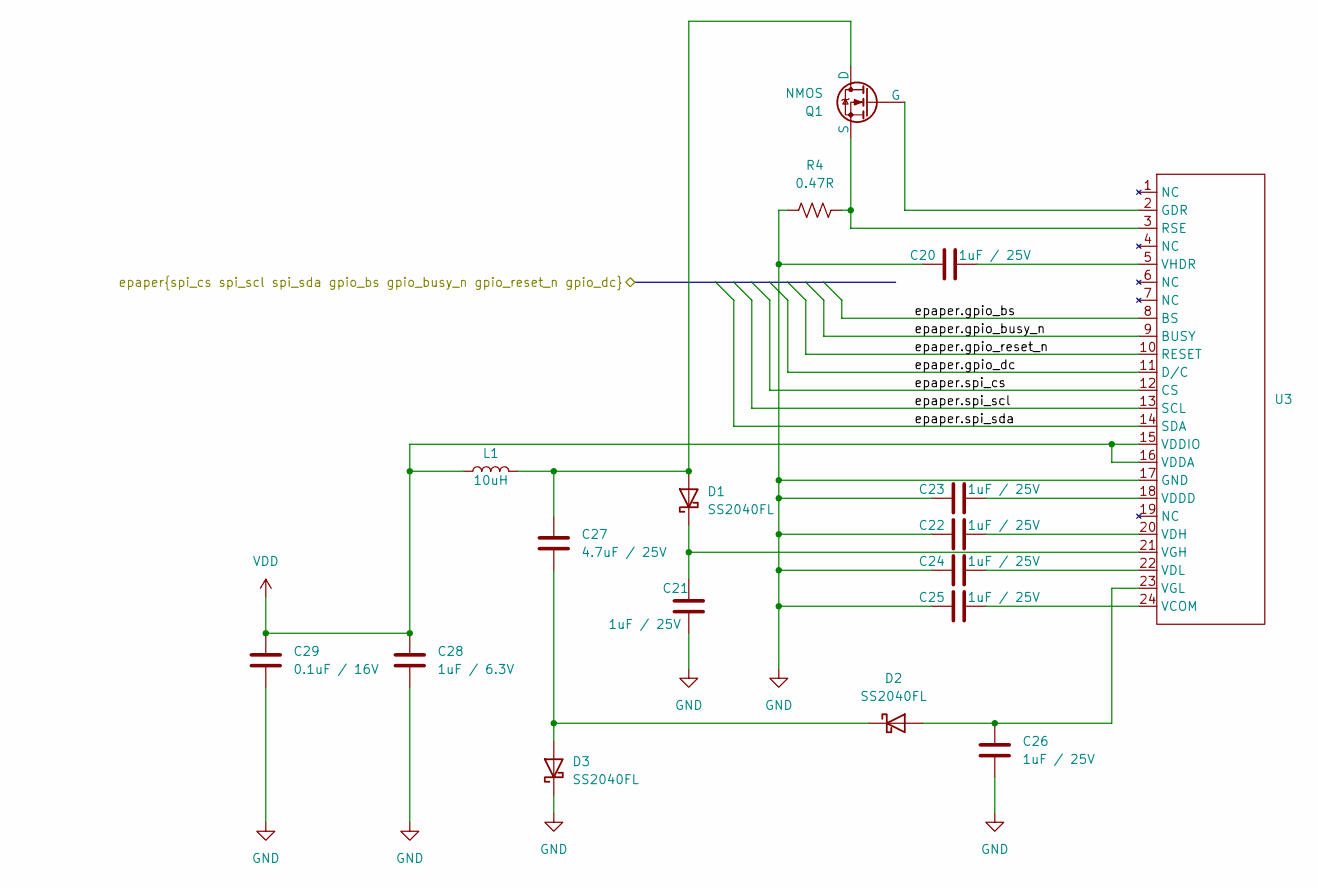
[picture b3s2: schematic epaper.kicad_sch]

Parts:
C20, C21, C22, C23, C24, C25, C26: 1uF / 25V; C_0603_1608Metric; Part Number C1608X7R1E105K080AE
C27: 4.7uF / 25V; C_0603_1608Metric; Part Number C1608X5R1E475K080AC
C28: 1uF / 6.3V; C_0201_0603Metric; Part Number KGM03BR50J105KH
C29: 0.1uF / 16V; C_0201_0603Metric; Part Number MSASE063SB5104KFNA01
D1, D2, D3: SS2040FL; D_SOD-123; Part Number SS2040FL_R1_00001
L1: 10uH; SDR0302; Part Number SDR0302-100ML
Q1: NMOS; SOT-323_SC-70; Part Number RTF016N05TL
R4: 0.47R; R_0805_2012Metric; Part Number ERJ-U6QJR47V
U3: F34G-1A7Q1-E8C24; Part Number E2154QS0F1, F34G-1A7Q1-E8C24

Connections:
/epaper/epaper.gpio_bs: U3.8 (BS); also elsewhere on the board
/epaper/epaper.gpio_busy_n: U3.9 (BUSY); also elsewhere on the board
/epaper/epaper.gpio_dc: U3.11 (D/C); also elsewhere on the board
/epaper/epaper.gpio_reset_n: U3.10 (RESET); also elsewhere on the board
/epaper/epaper.spi_cs: U3.12 (CS); also elsewhere on the board
/epaper/epaper.spi_scl: U3.13 (SCL); also elsewhere on the board
/epaper/epaper.spi_sda: U3.14 (SDA); also elsewhere on the board
GND: C20.1, C21.1, C22.1, C23.1, C24.1, C25.1, C26.1, C28.2, C29.2, D3.1 (K), R4.1, U3.17 (GND); also elsewhere on the board
unnamed: C27.1, D1.2 (A), L1.2, Q1.3 (D)
unnamed: C21.2, D1.1 (K), U3.21 (VGH)
unnamed: C26.2, D2.2 (A), U3.23 (VGL)
unnamed: C27.2, D2.1 (K), D3.2 (A)
unnamed: Q1.1 (G), U3.2 (GDR)
unnamed: Q1.2 (S), R4.2, U3.3 (RSE)
unnamed: C25.2, U3.24 (VCOM)
unnamed: C23.2, U3.18 (VDDD)
unnamed: C22.2, U3.20 (VDH)
unnamed: C24.2, U3.22 (VDL)
unnamed: C20.2, U3.5 (VHDR)
VDD: C28.1, C29.1, L1.1, U3.15 (VDDIO), U3.16 (VDDA); also elsewhere on the board

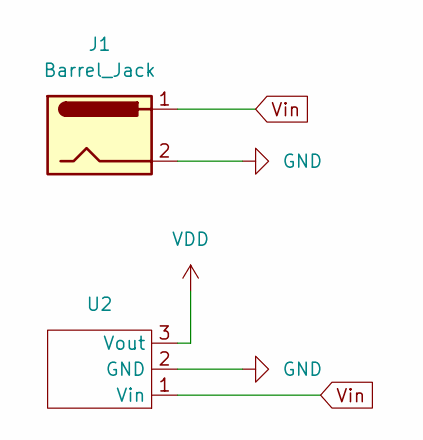
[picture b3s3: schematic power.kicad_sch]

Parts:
J1: Barrel_Jack; BarrelJack_Horizontal; Part Number CON-SOCJ-2155
U2: SOT-223; Part Number SPX2945M3-L-3-3/TR

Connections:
GND: J1.2, U2.2 (GND); also elsewhere on the board
VDD: U2.3 (Vout); also elsewhere on the board
Vin: J1.1, U2.1 (Vin)
